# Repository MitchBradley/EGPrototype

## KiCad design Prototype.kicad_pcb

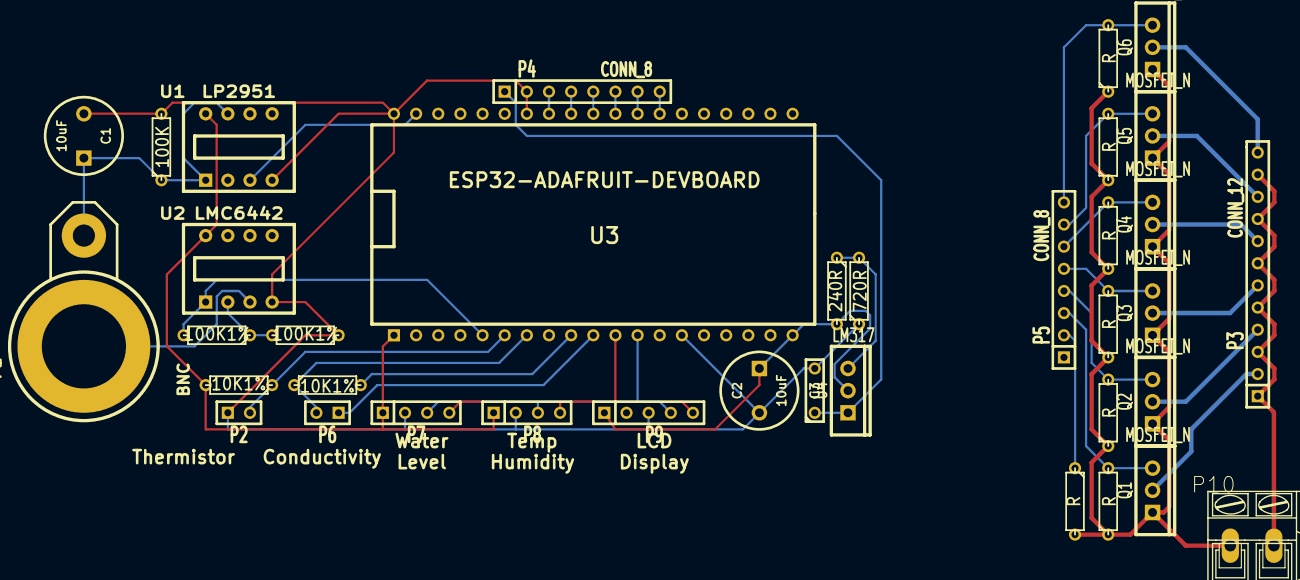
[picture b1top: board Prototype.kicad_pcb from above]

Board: 2 copper layers, 37 parts (0 on the bottom side), 37 nets.

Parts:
C1, C2: 10uF; C2V8
C3: 0.1uF; C2
P1: BNC; bnc
P2, P6: CONN_2; SIL-2
P3: CONN_12; SIL-12
P4, P5: CONN_8; SIL-8
P7, P8: CONN_4; SIL-4
P9: CONN_5; SIL-5
P10: CONN_2; AK300-2
Q1, Q2, Q3, Q4, Q5, Q6: MOSFET_N; TO220_GDS
R1: 100K; R3
R2, R3, R5, R9, R10, R11, R12: R; R3
R4, R7: 10K1%; R3
R6, R8: 100K1%; R3
R13: 240R; R3
R14: 720R; R3
U1: LP2951; SWDIP4
U2: LMC6442; SWDIP4
U3: ESP32-ADAFRUIT-DEVBOARD; DIP-38__1000
U4: LM317; TO220_VERT

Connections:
/+12V: C3.1, P4.1, U4.1
/ADDWATER: P4.8, U3.26
/CIRCULATE: P4.6, U3.28
/MOTOR-: P10.1, Q1.S, Q2.S, Q3.S, Q4.S, Q5.S, Q6.S, R2.1, R3.1, R5.1, R9.1, R10.1, R11.1, R12.2
/NUTRIENT: P4.5, U3.29
/SCL: P7.4, P8.4, P9.5, U3.11
/SDA: P7.3, P8.3, P9.4, U3.12
/SPRAY: P4.7, U3.27
/pHDN: P4.4, U3.30
/pHUP: P4.3, U3.31
AGND: C1.2, C2.2, C3.2, P2.1, P4.2, P7.2, P8.2, P9.3, R1.2, R6.1, R14.1, U1.4, U2.4, U3.14, U3.32, U3.38
unnamed: P7.1, P8.1, R4.2, U1.8, U2.8, U3.1
unnamed: P2.2, R4.1, U3.6
unnamed: P6.1, U3.10
unnamed: R7.2, U3.9
unnamed: P6.2, R7.1, U3.7
unnamed: P5.3, Q1.G, R2.2
unnamed: R8.2, U2.1, U3.5
unnamed: R6.2, R8.1, U2.2
unnamed: P5.2, R12.1
unnamed: P1.2, U2.3
unnamed: U1.3, U3.37
unnamed: C1.1, P1.1, R1.1, U1.1, U1.7
unnamed: R13.1, R14.2, U4.2
unnamed: P3.1, P3.3, P3.5, P3.7, P3.9, P3.11, P5.1, P10.2
unnamed: P3.2, Q1.D
unnamed: P5.8, Q6.G, R11.2
unnamed: P5.4, Q2.G, R3.2
unnamed: P5.5, Q3.G, R5.2
unnamed: P5.6, Q4.G, R9.2
unnamed: P3.8, Q4.D
unnamed: P5.7, Q5.G, R10.2
unnamed: P3.12, Q6.D
unnamed: P3.10, Q5.D
unnamed: C2.1, P9.1, R13.2, U3.19, U4.3
unnamed: P3.4, Q2.D
unnamed: P3.6, Q3.D

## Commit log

2017-08-10 Initial checkin
